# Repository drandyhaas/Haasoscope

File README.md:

# Haasoscope

Docs, design, firmware, and software for the Haasoscope!
Read the guide here: https://goo.gl/1Ry1k4 

Original funding campaign: https://www.crowdsupply.com/andy-haas/haasoscope (see the "updates" tab for lots of info)
Now also for sale on eBay - just search for "Haasoscope": https://www.ebay.com/sch/i.html?_nkw=haasoscope

A changelog for the python code is here: https://docs.google.com/document/d/18tjrI03KipmFqbNIHOzAKYy1VVE9wWbefSHazbPP8Gc/edit?usp=sharing and it also has pointers to changelogs for the firmware, board, and android app.

3D printable cases are available (see the guide for info)

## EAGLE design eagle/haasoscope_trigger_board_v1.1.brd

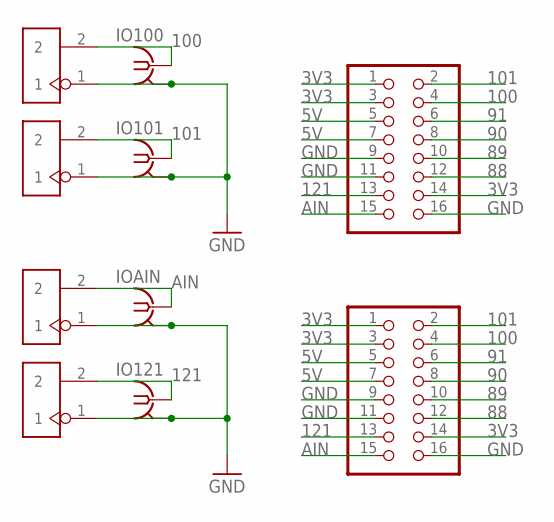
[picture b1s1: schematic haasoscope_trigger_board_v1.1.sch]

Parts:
IO100, IO101, IO121: BU-SMB-V
IOAIN: BU-SMB-V
J1, J2, J3, J4: 2p-2.54; H2-2.54
JP1: Jp1; 2X08
JP2: JP2; 2X08

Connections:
3V3: JP1.1, JP1.3, JP1.14, JP2.1, JP2.3, JP2.14
5V: JP1.5, JP1.7, JP2.5, JP2.7
88: JP1.12, JP2.12
89: JP1.10, JP2.10
90: JP1.8, JP2.8
91: JP1.6, JP2.6
100: IO100.1, J1.2, JP1.4, JP2.4
101: IO101.1, J2.2, JP1.2, JP2.2
121: IO121.1, J4.2, JP1.13, JP2.13
AIN: IOAIN.1, J3.2, JP1.15, JP2.15
GND: IO100.2, IO100.3 (2), IO100.4 (2), IO100.5 (2), IO101.2, IO101.3 (2), IO101.4 (2), IO101.5 (2), IO121.2, IO121.3 (2), IO121.4 (2), IO121.5 (2), IOAIN.2, IOAIN.3 (2), IOAIN.4 (2), IOAIN.5 (2), J1.1, J2.1, J3.1, J4.1, JP1.9, JP1.11, JP1.16, JP2.9, JP2.11, JP2.16

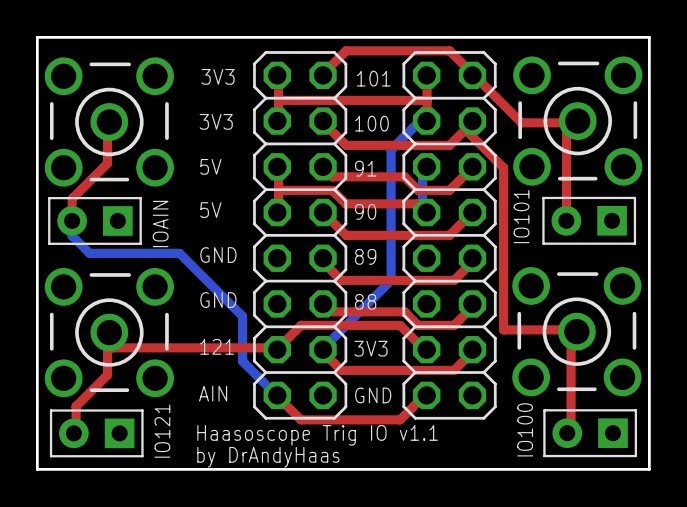
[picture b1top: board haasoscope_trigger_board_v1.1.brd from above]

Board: 2 copper layers, 34.0 x 24.0 mm, 10 parts (0 on the bottom side), 11 nets.

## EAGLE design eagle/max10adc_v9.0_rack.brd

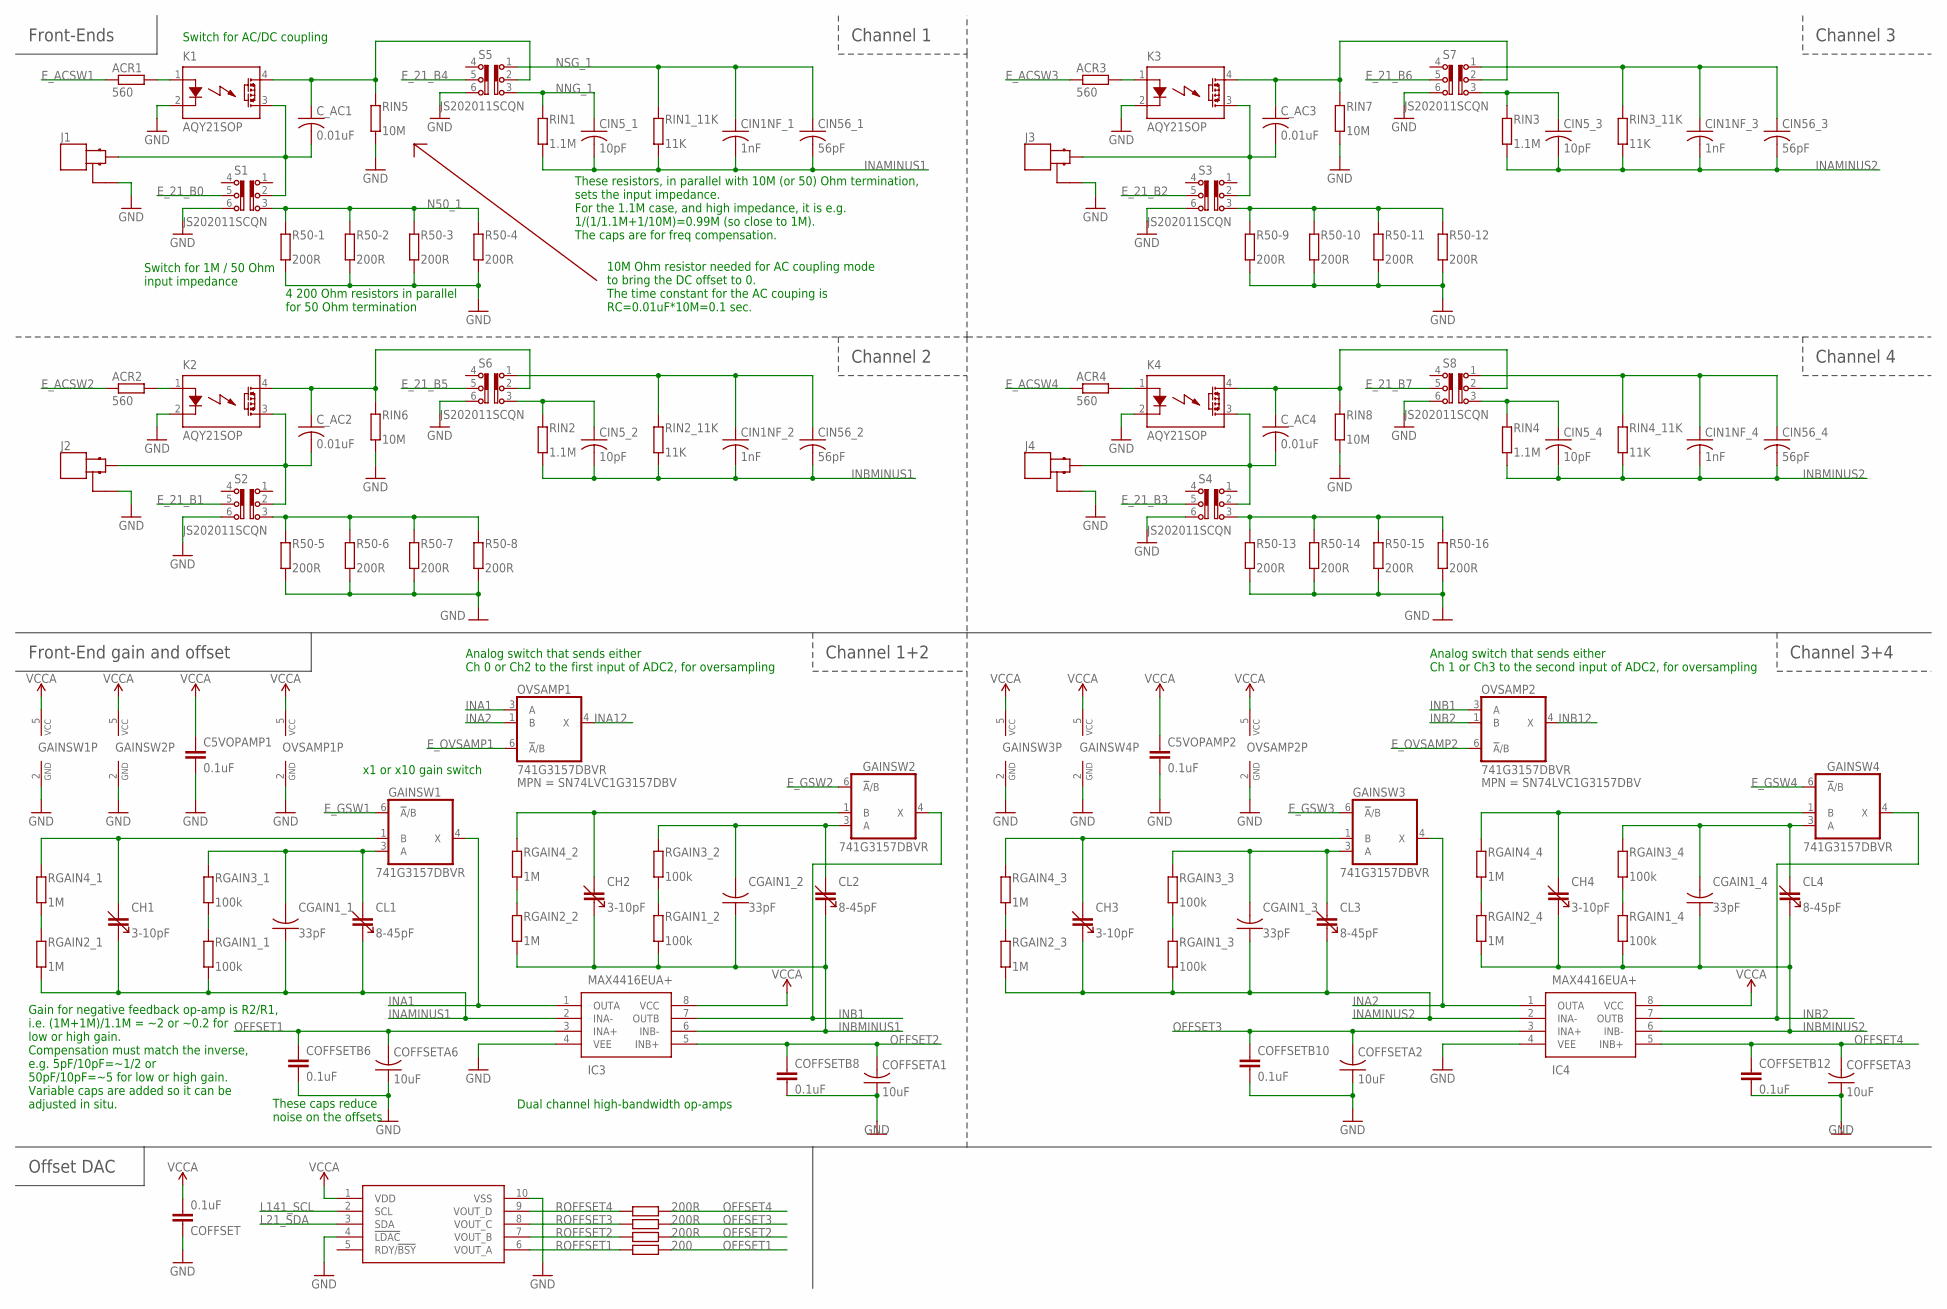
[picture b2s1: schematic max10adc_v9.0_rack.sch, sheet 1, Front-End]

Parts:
ACR1, ACR2, ACR3, ACR4: 560; R0805; MPN MF-RES-0805-560
C5VOPAMP1, C5VOPAMP2: 0.1uF; C0805K; MPN MF-CAP-0805-0.1uF
CGAIN1_1, CGAIN1_2, CGAIN1_3, CGAIN1_4: 33pF; C0603; MPN 06033A330JAT2A
CH1, CH2, CH3, CH4: 3-10pF; CTZ3; MPN TZY2Z100AC01
CIN1NF_1, CIN1NF_2, CIN1NF_3, CIN1NF_4: 1nF; C0603; MPN 06035A102JAT2A
CIN5_1, CIN5_2, CIN5_3, CIN5_4: 10pF; C0603; MPN MF-CAP-0603-10pF
CIN56_1, CIN56_2, CIN56_3, CIN56_4: 56pF; C0603; MPN 06035A560FAT2A
CL1, CL2, CL3, CL4: 8-45pF; CTZ3; MPN TZY2K450AC01
COFFSET: 0.1uF; C0805K; MPN MF-CAP-0805-0.1uF
COFFSETA1, COFFSETA2, COFFSETA3, COFFSETA6: 10uF; C1206; MPN MF-CAP-1206-10uF
COFFSETB6, COFFSETB8, COFFSETB10, COFFSETB12: 0.1uF; C0805K; MPN MF-CAP-0805-0.1uF
C_AC1, C_AC2, C_AC3, C_AC4: 0.01uF; C0603
DAC1: MCP4728; MSOP10
GAINSW1, GAINSW2, GAINSW3, GAINSW4: 741G3157DBVR; DBV_R-PDSO-G6; MPN SN74LVC1G3157DBV
IC3, IC4: MAX4416EUA+; SOP65P490X110-8N
J1, J2, J3, J4: MOLEX_BNC_73100-0105; MOLEX-BNC-73100-0105; MPN 73100-0105
K1, K2, K3, K4: AQY21SOP; SOP04; MPN AQY210S
OVSAMP1, OVSAMP2: 741G3157DBVR; DBV_R-PDSO-G6; MPN SN74LVC1G3157DBV
R50-1, R50-2, R50-3, R50-4, R50-5, R50-6, R50-7, R50-8, R50-9, R50-10, R50-11, R50-12, R50-13, R50-14, R50-15, R50-16: 200R; R0805
RGAIN1_1, RGAIN1_2, RGAIN1_3, RGAIN1_4, RGAIN3_1, RGAIN3_2, RGAIN3_3, RGAIN3_4: 100k; R0805; MPN MF-RES-0805-100k
RGAIN2_1, RGAIN2_2, RGAIN2_3, RGAIN2_4, RGAIN4_1, RGAIN4_2, RGAIN4_3, RGAIN4_4: 1M; R0805; MPN MF-RES-0805-1M
RIN1, RIN2, RIN3, RIN4: 1.1M; R0805; MPN CRCW08051M10FKEA
RIN1_11K, RIN2_11K, RIN3_11K, RIN4_11K: 11K; R0805; MPN CRCW080511K0FKEA
RIN5, RIN6, RIN7, RIN8: 10M; R0805; MPN CRCW080510M0FKEB
ROFFSET1: 200; R0805
ROFFSET2, ROFFSET3, ROFFSET4: 200R; R0805
S1, S2, S3, S4, S5, S6, S7, S8: JS202011SCQN

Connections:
CGAIN1: CGAIN1_1.2, CL1.- (4), GAINSW1.3 (A), RGAIN3_1.1
CGAIN2: CH1.- (4), GAINSW1.1 (B), RGAIN4_1.1
CGAIN3: CGAIN1_2.2, CL2.- (4), GAINSW2.3 (A), RGAIN3_2.1
CGAIN4: CH2.- (4), GAINSW2.1 (B), RGAIN4_2.1
CGAIN5: CGAIN1_3.2, CL3.- (4), GAINSW3.3 (A), RGAIN3_3.1
CGAIN6: CH3.- (4), GAINSW3.1 (B), RGAIN4_3.1
CGAIN7: CGAIN1_4.2, CL4.- (4), GAINSW4.3 (A), RGAIN3_4.1
CGAIN8: CH4.- (4), GAINSW4.1 (B), RGAIN4_4.1
E_21_B0: S1.5; also elsewhere on the board
E_21_B1: S2.5; also elsewhere on the board
E_21_B2: S3.5; also elsewhere on the board
E_21_B3: S4.5; also elsewhere on the board
E_21_B4: S5.5; also elsewhere on the board
E_21_B5: S6.5; also elsewhere on the board
E_21_B6: S7.5; also elsewhere on the board
E_21_B7: S8.5; also elsewhere on the board
E_ACSW1: ACR1.1; also elsewhere on the board
E_ACSW2: ACR2.1; also elsewhere on the board
E_ACSW3: ACR3.1; also elsewhere on the board
E_ACSW4: ACR4.1; also elsewhere on the board
E_GSW1: GAINSW1.6 (!A!/B); also elsewhere on the board
E_GSW2: GAINSW2.6 (!A!/B); also elsewhere on the board
E_GSW3: GAINSW3.6 (!A!/B); also elsewhere on the board
E_GSW4: GAINSW4.6 (!A!/B); also elsewhere on the board
E_OVSAMP1: OVSAMP1.6 (!A!/B); also elsewhere on the board
E_OVSAMP2: OVSAMP2.6 (!A!/B); also elsewhere on the board
GND: C5VOPAMP1.2, C5VOPAMP2.2, COFFSET.1, COFFSETA1.1, COFFSETA2.1, COFFSETA3.1, COFFSETA6.1, COFFSETB6.1, COFFSETB8.1, COFFSETB10.1, COFFSETB12.1, DAC1.4 (!LDAC), DAC1.10 (VSS), GAINSW1.2 (GND), GAINSW2.2 (GND), GAINSW3.2 (GND), GAINSW4.2 (GND), IC3.4 (VEE), IC4.4 (VEE), J1.GND1 (GND), J1.GND2 (GND), J2.GND1 (GND), J2.GND2 (GND), J3.GND1 (GND), J3.GND2 (GND), J4.GND1 (GND), J4.GND2 (GND), K1.2 (K), K2.2 (K), K3.2 (K), K4.2 (K), OVSAMP1.2 (GND), OVSAMP2.2 (GND), R50-1.2, R50-2.2, R50-3.2, R50-4.2, R50-5.2, R50-6.2, R50-7.2, R50-8.2, R50-9.2, R50-10.2, R50-11.2, R50-12.2, R50-13.2, R50-14.2, R50-15.2, R50-16.2, RIN5.2, RIN6.2, RIN7.2, RIN8.2, S1.6, S2.6, S3.6, S4.6, S5.6, S6.6, S7.6, S8.6; also elsewhere on the board
INA1: GAINSW1.4 (X), IC3.1 (OUTA), OVSAMP1.3 (A); also elsewhere on the board
INA2: GAINSW3.4 (X), IC4.1 (OUTA), OVSAMP1.1 (B)
INA12: OVSAMP1.4 (X); also elsewhere on the board
INAMINUS1: CGAIN1_1.1, CH1.+ (3), CIN1NF_1.2, CIN5_1.2, CIN56_1.2, CL1.+ (3), IC3.2 (INA-), RGAIN1_1.2, RGAIN2_1.2, RIN1.2, RIN1_11K.2
INAMINUS2: CGAIN1_3.1, CH3.+ (3), CIN1NF_3.2, CIN5_3.2, CIN56_3.2, CL3.+ (3), IC4.2 (INA-), RGAIN1_3.2, RGAIN2_3.2, RIN3.2, RIN3_11K.2
INB1: GAINSW2.4 (X), IC3.7 (OUTB), OVSAMP2.3 (A); also elsewhere on the board
INB2: GAINSW4.4 (X), IC4.7 (OUTB), OVSAMP2.1 (B)
INB12: OVSAMP2.4 (X); also elsewhere on the board
INBMINUS1: CGAIN1_2.1, CH2.+ (3), CIN1NF_2.2, CIN5_2.2, CIN56_2.2, CL2.+ (3), IC3.6 (INB-), RGAIN1_2.2, RGAIN2_2.2, RIN2.2, RIN2_11K.2
INBMINUS2: CGAIN1_4.1, CH4.+ (3), CIN1NF_4.2, CIN5_4.2, CIN56_4.2, CL4.+ (3), IC4.6 (INB-), RGAIN1_4.2, RGAIN2_4.2, RIN4.2, RIN4_11K.2
INJ1: C_AC1.2, J1.SIGNAL, K1.3 (DS2), S1.2
INJ2: C_AC2.2, J2.SIGNAL, K2.3 (DS2), S2.2
INJ3: C_AC3.2, J3.SIGNAL, K3.3 (DS2), S3.2
INJ4: C_AC4.2, J4.SIGNAL, K4.3 (DS2), S4.2
L21_SDA: DAC1.3 (SDA); also elsewhere on the board
L141_SCL: DAC1.2 (SCL); also elsewhere on the board
N50_1: R50-1.1, R50-2.1, R50-3.1, R50-4.1, S1.3
unnamed: RGAIN1_1.1, RGAIN3_1.2
unnamed: RGAIN2_1.1, RGAIN4_1.2
unnamed: RGAIN1_2.1, RGAIN3_2.2
unnamed: RGAIN2_2.1, RGAIN4_2.2
unnamed: RGAIN1_3.1, RGAIN3_3.2
unnamed: RGAIN2_3.1, RGAIN4_3.2
unnamed: RGAIN1_4.1, RGAIN3_4.2
unnamed: RGAIN2_4.1, RGAIN4_4.2
unnamed: C_AC1.1, K1.4 (DS1), RIN5.1, S5.2
unnamed: ACR1.2, K1.1 (A)
unnamed: C_AC2.1, K2.4 (DS1), RIN6.1, S6.2
unnamed: CIN1NF_2.1, CIN56_2.1, RIN2_11K.1, S6.1
unnamed: ACR2.2, K2.1 (A)
unnamed: CIN5_2.1, RIN2.1, S6.3
unnamed: R50-5.1, R50-6.1, R50-7.1, R50-8.1, S2.3
unnamed: R50-9.1, R50-10.1, R50-11.1, R50-12.1, S3.3
unnamed: R50-13.1, R50-14.1, R50-15.1, R50-16.1, S4.3
unnamed: ACR3.2, K3.1 (A)
unnamed: ACR4.2, K4.1 (A)
unnamed: C_AC3.1, K3.4 (DS1), RIN7.1, S7.2
unnamed: CIN1NF_3.1, CIN56_3.1, RIN3_11K.1, S7.1
unnamed: DAC1.6 (VOUT_A), ROFFSET1.2
unnamed: DAC1.7 (VOUT_B), ROFFSET2.2
unnamed: DAC1.8 (VOUT_C), ROFFSET3.2
unnamed: DAC1.9 (VOUT_D), ROFFSET4.2
unnamed: C_AC4.1, K4.4 (DS1), RIN8.1, S8.2
unnamed: CIN5_3.1, RIN3.1, S7.3
unnamed: CIN1NF_4.1, CIN56_4.1, RIN4_11K.1, S8.1
unnamed: CIN5_4.1, RIN4.1, S8.3
NNG_1: CIN5_1.1, RIN1.1, S5.3
NSG_1: CIN1NF_1.1, CIN56_1.1, RIN1_11K.1, S5.1
OFFSET1: COFFSETA6.2, COFFSETB6.2, IC3.3 (INA+), ROFFSET1.1
OFFSET2: COFFSETA1.2, COFFSETB8.2, IC3.5 (INB+), ROFFSET2.1
OFFSET3: COFFSETA2.2, COFFSETB10.2, IC4.3 (INA+), ROFFSET3.1
OFFSET4: COFFSETA3.2, COFFSETB12.2, IC4.5 (INB+), ROFFSET4.1
VCCA: C5VOPAMP1.1, C5VOPAMP2.1, COFFSET.2, DAC1.1 (VDD), GAINSW1.5 (VCC), GAINSW2.5 (VCC), GAINSW3.5 (VCC), GAINSW4.5 (VCC), IC3.8 (VCC), IC4.8 (VCC), OVSAMP1.5 (VCC), OVSAMP2.5 (VCC); also elsewhere on the board

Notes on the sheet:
Front-Ends
Channel 3
Channel 1
Channel 2
Channel 4
Front-End gain and offset
Channel 1+2
Channel 3+4
Offset DAC
4 200 Ohm resistors in parallel for 50 Ohm termination
10M Ohm resistor needed for AC coupling mode to bring the DC offset to 0. The time constant for the AC couping is RC=0.01uF*10M=0.1 sec.
These resistors, in parallel with 10M (or 50) Ohm termination, sets the input impedance. For the 1.1M case, and high impedance, it is e.g. 1/(1/1.1M+1/10M)=0.99M (so close to 1M). The caps are for freq compensation.
Switch for AC/DC coupling
Switch for 1M / 50 Ohm input impedance
Analog switch that sends either Ch 0 or Ch2 to the first input of ADC2, for oversampling
Analog switch that sends either Ch 1 or Ch3 to the second input of ADC2, for oversampling
Dual channel high-bandwidth op-amps
x1 or x10 gain switch
These caps reduce noise on the offsets
Gain for negative feedback op-amp is R2/R1, i.e. (1M+1M)/1.1M = ~2 or ~0.2 for low or high gain. Compensation must match the inverse, e.g. 5pF/10pF=~1/2 or 50pF/10pF=~5 for low or high gain. Variable caps are added so it can be adjusted in situ.

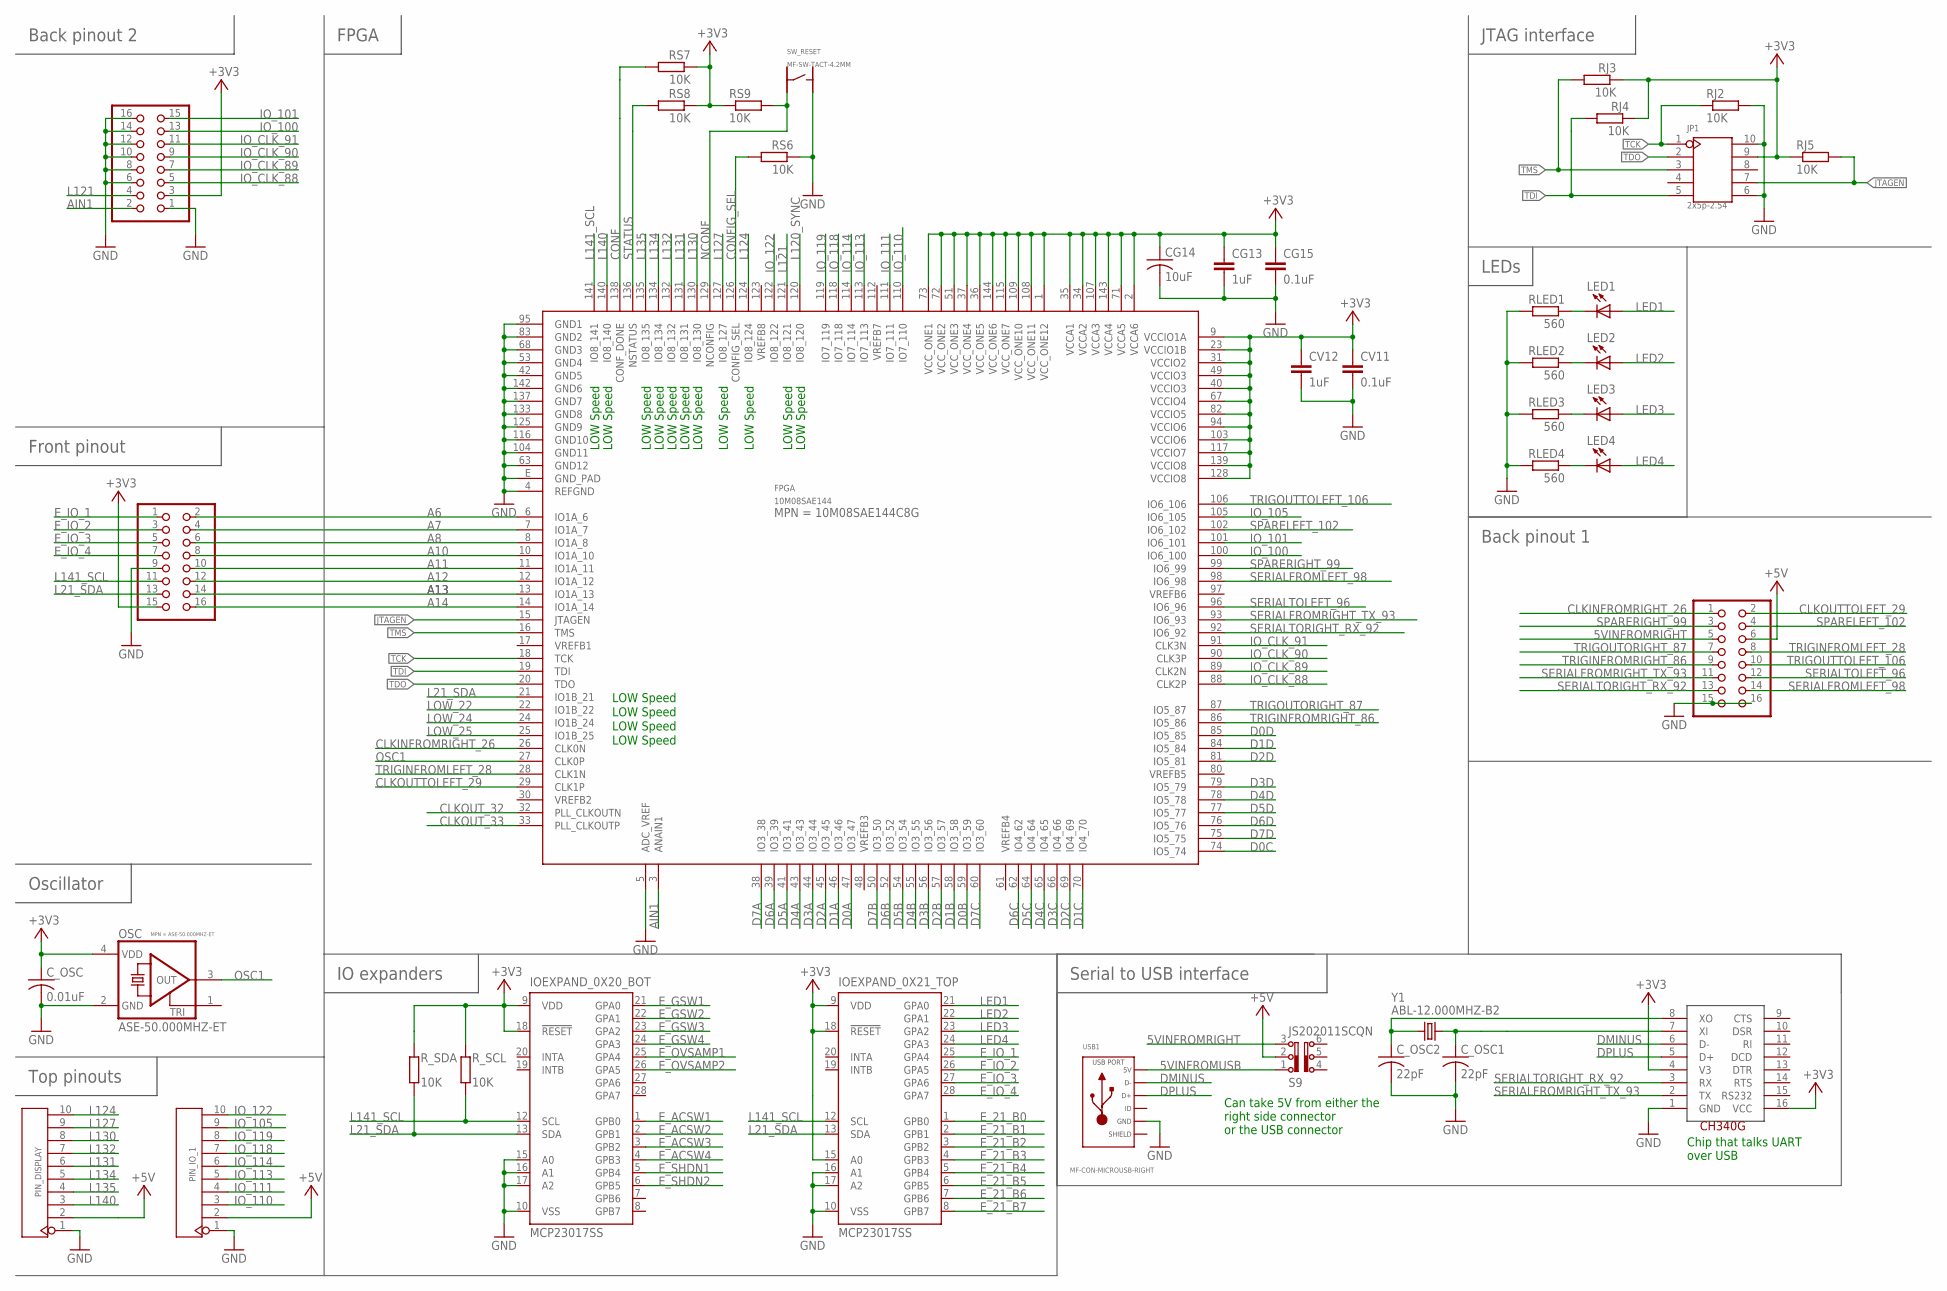
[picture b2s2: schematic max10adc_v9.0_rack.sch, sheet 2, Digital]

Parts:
CG13: 1uF; C0805K; MPN MF-CAP-0805-1uF
CG14: 10uF; C1206; MPN MF-CAP-1206-10uF
CG15: 0.1uF; C0805K; MPN MF-CAP-0805-0.1uF
CV11: 0.1uF; C0805K; MPN MF-CAP-0805-0.1uF
CV12: 1uF; C0805K; MPN MF-CAP-0805-1uF
C_OSC: 0.01uF; C0603
C_OSC1, C_OSC2: 22pF; C0603
FPGA: 10M08SAE144; EQFP144; MPN 10M08SAE144C8G
IOEXPAND_0X20_BOT, IOEXPAND_0X21_TOP: MCP23017SS; SSOP28
JP1: 2x5p-2.54; H2X5-2.54
LED1, LED2, LED3, LED4: MF-LED-0805-RED; SML0805; MPN MF-LED-0805-RED
OSC: ASE-50.000MHZ-ET; ASE; MPN ASE-50.000MHZ-ET
PIN_AIN_IO2_PWRGND: 15-91-2160; 2X08/90; MPN 15-91-2160
PIN_ANALOG_IOEXP, PIN_ANALOG_IOEXP1: 15-91-2160; 2X08/90; MPN 15-91-2160
PIN_DISPLAY: YELLOW-10P-2.54; H10-2.54
PIN_IO_1: YELLOW-10P-2.54; H10-2.54
RJ2, RJ3, RJ4, RJ5: 10K; R0805; MPN MF-RES-0805-10K
RLED1, RLED2, RLED3, RLED4: 560; R0805; MPN MF-RES-0805-560
RS6, RS7, RS8, RS9: 10K; R0805; MPN MF-RES-0805-10K
R_SCL: 10K; R0805; MPN MF-RES-0805-10K
R_SDA: 10K; R0805; MPN MF-RES-0805-10K
S9: JS202011SCQN
SW_RESET: MF-SW-TACT-4.2MM; TACT4.2MM
U340G: CH340G; SOIC16
USB1: MF-CON-MICROUSB-RIGHT; 10118193-0001LF
Y1: ABL-12.000MHZ-B2; HC49US

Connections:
5VINFROMRIGHT: PIN_ANALOG_IOEXP1.5, S9.3
5VINFROMUSB: S9.1, USB1.1 (5V)
+3V3: CG13.1, CG14.1, CG15.1, CV11.1, CV12.1, C_OSC.1, FPGA.1 (VCC_ONE12), FPGA.2 (VCCA6), FPGA.9 (VCCIO1A), FPGA.23 (VCCIO1B), FPGA.31 (VCCIO2), FPGA.34 (VCCA2), FPGA.35 (VCCA1), FPGA.36 (VCC_ONE5), FPGA.37 (VCC_ONE4), FPGA.40 (VCCIO3), FPGA.49 (VCCIO3), FPGA.51 (VCC_ONE3), FPGA.67 (VCCIO4), FPGA.71 (VCCA5), FPGA.72 (VCC_ONE2), FPGA.73 (VCC_ONE1), FPGA.82 (VCCIO5), FPGA.94 (VCCIO6), FPGA.103 (VCCIO6), FPGA.107 (VCCA3), FPGA.108 (VCC_ONE11), FPGA.109 (VCC_ONE10), FPGA.115 (VCC_ONE7), FPGA.117 (VCCIO7), FPGA.128 (VCCIO8), FPGA.139 (VCCIO8), FPGA.143 (VCCA4), FPGA.144 (VCC_ONE6), IOEXPAND_0X20_BOT.9 (VDD), IOEXPAND_0X20_BOT.18 (!RESET), IOEXPAND_0X21_TOP.9 (VDD), IOEXPAND_0X21_TOP.15 (A0), IOEXPAND_0X21_TOP.18 (!RESET), JP1.9, OSC.4 (VDD), PIN_AIN_IO2_PWRGND.3, PIN_ANALOG_IOEXP.15, RJ3.1, RJ4.1, RJ5.1, RS7.1, RS8.1, RS9.1, R_SCL.2, R_SDA.2, U340G.4 (V3), U340G.16 (VCC); also elsewhere on the board
+5V: PIN_ANALOG_IOEXP1.6, PIN_DISPLAY.2, PIN_IO_1.2, S9.2; also elsewhere on the board
A6: FPGA.6 (IO1A_6), PIN_ANALOG_IOEXP.2
A7: FPGA.7 (IO1A_7), PIN_ANALOG_IOEXP.4
A8: FPGA.8 (IO1A_8), PIN_ANALOG_IOEXP.6
A10: FPGA.10 (IO1A_10), PIN_ANALOG_IOEXP.8
A11: FPGA.11 (IO1A_11), PIN_ANALOG_IOEXP.10
A12: FPGA.12 (IO1A_12), PIN_ANALOG_IOEXP.12
A13: FPGA.13 (IO1A_13), PIN_ANALOG_IOEXP.14
A14: FPGA.14 (IO1A_14), PIN_ANALOG_IOEXP.16
AIN1: FPGA.3 (ANAIN1), PIN_AIN_IO2_PWRGND.2
CLKINFROMRIGHT_26: FPGA.26 (CLK0N), PIN_ANALOG_IOEXP1.1
CLKOUTTOLEFT_29: FPGA.29 (CLK1P), PIN_ANALOG_IOEXP1.2
CLKOUT_32: FPGA.32 (PLL_CLKOUTN); also elsewhere on the board
CLKOUT_33: FPGA.33 (PLL_CLKOUTP); also elsewhere on the board
CONF: FPGA.138 (CONF_DONE), RS7.2
CONFIG_SEL: FPGA.126 (CONFIG_SEL), RS6.2
D0A: FPGA.47 (IO3_47); also elsewhere on the board
D0B: FPGA.59 (IO3_59); also elsewhere on the board
D0C: FPGA.74 (IO5_74); also elsewhere on the board
D0D: FPGA.85 (IO5_85); also elsewhere on the board
D1A: FPGA.46 (IO3_46); also elsewhere on the board
D1B: FPGA.58 (IO3_58); also elsewhere on the board
D1C: FPGA.70 (IO4_70); also elsewhere on the board
D1D: FPGA.84 (IO5_84); also elsewhere on the board
D2A: FPGA.45 (IO3_45); also elsewhere on the board
D2B: FPGA.57 (IO3_57); also elsewhere on the board
D2C: FPGA.69 (IO4_69); also elsewhere on the board
D2D: FPGA.81 (IO5_81); also elsewhere on the board
D3A: FPGA.44 (IO3_44); also elsewhere on the board
D3B: FPGA.56 (IO3_56); also elsewhere on the board
D3C: FPGA.66 (IO4_66); also elsewhere on the board
D3D: FPGA.79 (IO5_79); also elsewhere on the board
D4A: FPGA.43 (IO3_43); also elsewhere on the board
D4B: FPGA.55 (IO3_55); also elsewhere on the board
D4C: FPGA.65 (IO4_65); also elsewhere on the board
D4D: FPGA.78 (IO5_78); also elsewhere on the board
D5A: FPGA.41 (IO3_41); also elsewhere on the board
D5B: FPGA.54 (IO3_54); also elsewhere on the board
D5C: FPGA.64 (IO4_64); also elsewhere on the board
D5D: FPGA.77 (IO5_77); also elsewhere on the board
D6A: FPGA.39 (IO3_39); also elsewhere on the board
D6B: FPGA.52 (IO3_52); also elsewhere on the board
D6C: FPGA.62 (IO4_62); also elsewhere on the board
D6D: FPGA.76 (IO5_76); also elsewhere on the board
D7A: FPGA.38 (IO3_38); also elsewhere on the board
D7B: FPGA.50 (IO3_50); also elsewhere on the board
D7C: FPGA.60 (IO3_60); also elsewhere on the board
D7D: FPGA.75 (IO5_75); also elsewhere on the board
DMINUS: U340G.6 (D-), USB1.2 (D-)
DPLUS: U340G.5 (D+), USB1.3 (D+)
E_21_B0: IOEXPAND_0X21_TOP.1 (GPB0); also elsewhere on the board
E_21_B1: IOEXPAND_0X21_TOP.2 (GPB1); also elsewhere on the board
E_21_B2: IOEXPAND_0X21_TOP.3 (GPB2); also elsewhere on the board
E_21_B3: IOEXPAND_0X21_TOP.4 (GPB3); also elsewhere on the board
E_21_B4: IOEXPAND_0X21_TOP.5 (GPB4); also elsewhere on the board
E_21_B5: IOEXPAND_0X21_TOP.6 (GPB5); also elsewhere on the board
E_21_B6: IOEXPAND_0X21_TOP.7 (GPB6); also elsewhere on the board
E_21_B7: IOEXPAND_0X21_TOP.8 (GPB7); also elsewhere on the board
E_ACSW1: IOEXPAND_0X20_BOT.1 (GPB0); also elsewhere on the board
E_ACSW2: IOEXPAND_0X20_BOT.2 (GPB1); also elsewhere on the board
E_ACSW3: IOEXPAND_0X20_BOT.3 (GPB2); also elsewhere on the board
E_ACSW4: IOEXPAND_0X20_BOT.4 (GPB3); also elsewhere on the board
E_GSW1: IOEXPAND_0X20_BOT.21 (GPA0); also elsewhere on the board
E_GSW2: IOEXPAND_0X20_BOT.22 (GPA1); also elsewhere on the board
E_GSW3: IOEXPAND_0X20_BOT.23 (GPA2); also elsewhere on the board
E_GSW4: IOEXPAND_0X20_BOT.24 (GPA3); also elsewhere on the board
E_IO_1: IOEXPAND_0X21_TOP.25 (GPA4), PIN_ANALOG_IOEXP.1
E_IO_2: IOEXPAND_0X21_TOP.26 (GPA5), PIN_ANALOG_IOEXP.3
E_IO_3: IOEXPAND_0X21_TOP.27 (GPA6), PIN_ANALOG_IOEXP.5
E_IO_4: IOEXPAND_0X21_TOP.28 (GPA7), PIN_ANALOG_IOEXP.7
E_OVSAMP1: IOEXPAND_0X20_BOT.25 (GPA4); also elsewhere on the board
E_OVSAMP2: IOEXPAND_0X20_BOT.26 (GPA5); also elsewhere on the board
E_SHDN1: IOEXPAND_0X20_BOT.5 (GPB4); also elsewhere on the board
E_SHDN2: IOEXPAND_0X20_BOT.6 (GPB5); also elsewhere on the board
GND: CG13.2, CG14.2, CG15.2, CV11.2, CV12.2, C_OSC.2, C_OSC1.2, C_OSC2.2, FPGA.4 (REFGND), FPGA.5 (ADC_VREF), FPGA.42 (GND5), FPGA.53 (GND4), FPGA.63 (GND12), FPGA.68 (GND3), FPGA.83 (GND2), FPGA.95 (GND1), FPGA.104 (GND11), FPGA.116 (GND10), FPGA.125 (GND9), FPGA.133 (GND8), FPGA.137 (GND7), FPGA.142 (GND6), FPGA.E (GND_PAD), IOEXPAND_0X20_BOT.10 (VSS), IOEXPAND_0X20_BOT.15 (A0), IOEXPAND_0X20_BOT.16 (A1), IOEXPAND_0X20_BOT.17 (A2), IOEXPAND_0X21_TOP.10 (VSS), IOEXPAND_0X21_TOP.16 (A1), IOEXPAND_0X21_TOP.17 (A2), JP1.6, JP1.10, OSC.2 (GND), PIN_AIN_IO2_PWRGND.1, PIN_AIN_IO2_PWRGND.6, PIN_AIN_IO2_PWRGND.8, PIN_AIN_IO2_PWRGND.10, PIN_AIN_IO2_PWRGND.12, PIN_AIN_IO2_PWRGND.14, PIN_AIN_IO2_PWRGND.16, PIN_ANALOG_IOEXP.9, PIN_ANALOG_IOEXP1.15, PIN_ANALOG_IOEXP1.16, PIN_DISPLAY.1, PIN_IO_1.1, RJ2.2, RLED1.2, RLED2.2, RLED3.2, RLED4.2, RS6.1, SW_RESET.P$2, U340G.1 (GND), USB1.5 (GND); also elsewhere on the board
IO_100: FPGA.100 (IO6_100), PIN_AIN_IO2_PWRGND.13
IO_101: FPGA.101 (IO6_101), PIN_AIN_IO2_PWRGND.15
IO_105: FPGA.105 (IO6_105), PIN_IO_1.9
IO_110: FPGA.110 (IO7_110), PIN_IO_1.3
IO_111: FPGA.111 (IO7_111), PIN_IO_1.4
IO_113: FPGA.113 (IO7_113), PIN_IO_1.5
IO_114: FPGA.114 (IO7_114), PIN_IO_1.6
IO_118: FPGA.118 (IO7_118), PIN_IO_1.7
IO_119: FPGA.119 (IO7_119), PIN_IO_1.8
IO_122: FPGA.122 (IO8_122), PIN_IO_1.10
IO_CLK_88: FPGA.88 (CLK2P), PIN_AIN_IO2_PWRGND.5
IO_CLK_89: FPGA.89 (CLK2N), PIN_AIN_IO2_PWRGND.7
IO_CLK_90: FPGA.90 (CLK3P), PIN_AIN_IO2_PWRGND.9
IO_CLK_91: FPGA.91 (CLK3N), PIN_AIN_IO2_PWRGND.11
JTAGEN: FPGA.15 (JTAGEN), JP1.7, RJ5.2
L21_SDA: FPGA.21 (IO1B_21), IOEXPAND_0X20_BOT.13 (SDA), IOEXPAND_0X21_TOP.13 (SDA), PIN_ANALOG_IOEXP.13, R_SDA.1; also elsewhere on the board
L120_SYNC: FPGA.120 (IO8_120); also elsewhere on the board
L121: FPGA.121 (IO8_121), PIN_AIN_IO2_PWRGND.4
L124: FPGA.124 (IO8_124), PIN_DISPLAY.10
L127: FPGA.127 (IO8_127), PIN_DISPLAY.9
L130: FPGA.130 (IO8_130), PIN_DISPLAY.8
L131: FPGA.131 (IO8_131), PIN_DISPLAY.6
L132: FPGA.132 (IO8_132), PIN_DISPLAY.7
L134: FPGA.134 (IO8_134), PIN_DISPLAY.5
L135: FPGA.135 (IO8_135), PIN_DISPLAY.4
L140: FPGA.140 (IO8_140), PIN_DISPLAY.3
L141_SCL: FPGA.141 (IO8_141), IOEXPAND_0X20_BOT.12 (SCL), IOEXPAND_0X21_TOP.12 (SCL), PIN_ANALOG_IOEXP.11, R_SCL.1; also elsewhere on the board
LED1: IOEXPAND_0X21_TOP.21 (GPA0), LED1.A
LED2: IOEXPAND_0X21_TOP.22 (GPA1), LED2.A
LED3: IOEXPAND_0X21_TOP.23 (GPA2), LED3.A
LED4: IOEXPAND_0X21_TOP.24 (GPA3), LED4.A
LOW_22: FPGA.22 (IO1B_22); also elsewhere on the board
LOW_24: FPGA.24 (IO1B_24); also elsewhere on the board
LOW_25: FPGA.25 (IO1B_25); also elsewhere on the board
unnamed: LED4.C, RLED4.1
unnamed: LED3.C, RLED3.1
unnamed: LED2.C, RLED2.1
unnamed: LED1.C, RLED1.1
unnamed: C_OSC1.1, U340G.7 (XI), Y1.1
unnamed: C_OSC2.1, U340G.8 (XO), Y1.2
NCONF: FPGA.129 (NCONFIG), RS9.2, SW_RESET.P$4
OSC1: FPGA.27 (CLK0P), OSC.3 (OUT)
SERIALFROMLEFT_98: FPGA.98 (IO6_98), PIN_ANALOG_IOEXP1.14
SERIALFROMRIGHT_TX_93: FPGA.93 (IO6_93), PIN_ANALOG_IOEXP1.11, U340G.2 (TX)
SERIALTOLEFT_96: FPGA.96 (IO6_96), PIN_ANALOG_IOEXP1.12
SERIALTORIGHT_RX_92: FPGA.92 (IO6_92), PIN_ANALOG_IOEXP1.13, U340G.3 (RX)
SLD: USB1.S1 (SLD), USB1.S2 (SLD), USB1.S3 (SLD), USB1.S4 (SLD)
SPARELEFT_102: FPGA.102 (IO6_102), PIN_ANALOG_IOEXP1.4
SPARERIGHT_99: FPGA.99 (IO6_99), PIN_ANALOG_IOEXP1.3
STATUS: FPGA.136 (NSTATUS), RS8.2
TCK: FPGA.18 (TCK), JP1.1, RJ2.1
TDI: FPGA.19 (TDI), JP1.5, RJ4.2
TDO: FPGA.20 (TDO), JP1.2
TMS: FPGA.16 (TMS), JP1.3, RJ3.2
TRIGINFROMLEFT_28: FPGA.28 (CLK1N), PIN_ANALOG_IOEXP1.8
TRIGINFROMRIGHT_86: FPGA.86 (IO5_86), PIN_ANALOG_IOEXP1.9
TRIGOUTORIGHT_87: FPGA.87 (IO5_87), PIN_ANALOG_IOEXP1.7
TRIGOUTTOLEFT_106: FPGA.106 (IO6_106), PIN_ANALOG_IOEXP1.10

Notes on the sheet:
LOW Speed
FPGA
Back pinout 2
Front pinout
Oscillator
Top pinouts
IO expanders
Serial to USB interface
LEDs
JTAG interface
Can take 5V from either the right side connector or the USB connector
Chip that talks UART over USB
Back pinout 1

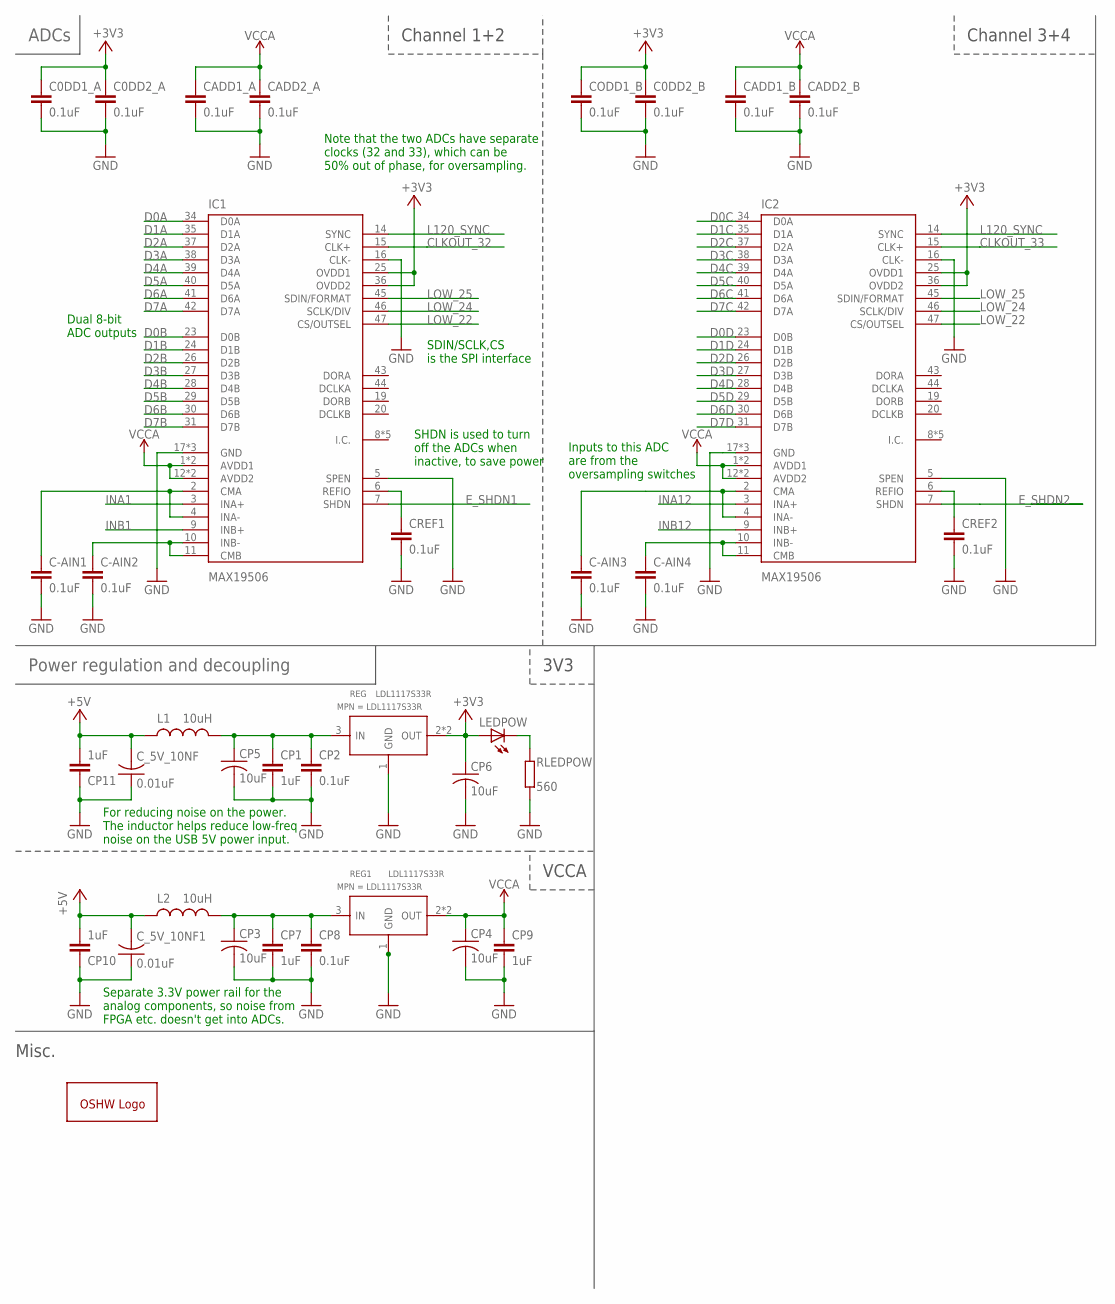
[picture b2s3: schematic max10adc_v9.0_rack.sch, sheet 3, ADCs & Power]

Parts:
C0DD1_A, C0DD2_A, C0DD2_B: 0.1uF; C0805K; MPN MF-CAP-0805-0.1uF
C-AIN1, C-AIN2, C-AIN3, C-AIN4: 0.1uF; C0805K; MPN MF-CAP-0805-0.1uF
CADD1_A, CADD1_B, CADD2_A, CADD2_B: 0.1uF; C0805K; MPN MF-CAP-0805-0.1uF
CODD1_B: 0.1uF; C0805K; MPN MF-CAP-0805-0.1uF
CP1, CP7, CP9, CP10, CP11: 1uF; C0805K; MPN MF-CAP-0805-1uF
CP2, CP8: 0.1uF; C0805K; MPN MF-CAP-0805-0.1uF
CP3, CP4, CP5, CP6: 10uF; C1206; MPN MF-CAP-1206-10uF
CREF1, CREF2: 0.1uF; C0805K; MPN MF-CAP-0805-0.1uF
C_5V_10NF, C_5V_10NF1: 0.01uF; C0603
GOLD_ORB_SM1: OSHWLOGOLOGO8MM; OSHW_8MM
IC1, IC2: MAX19506; TQFP-48; MPN MAX19506ETM+
L1, L2: 10uH; 1210; MPN MF-IND-1210-10uH
LEDPOW: MF-LED-0805-RED; SML0805; MPN MF-LED-0805-RED
REG, REG1: LDL1117S33R; SOT-223; MPN LDL1117S33R
RLEDPOW: 560; R0805; MPN MF-RES-0805-560

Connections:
+3V3: C0DD1_A.1, C0DD2_A.1, C0DD2_B.1, CODD1_B.1, CP6.1, IC1.25 (OVDD1), IC1.36 (OVDD2), IC2.25 (OVDD1), IC2.36 (OVDD2), LEDPOW.A, REG.2 (OUT), REG.TER (OUT); also elsewhere on the board
+5V: CP10.2, CP11.2, C_5V_10NF.2, C_5V_10NF1.2, L1.1, L2.1; also elsewhere on the board
CLKOUT_32: IC1.15 (CLK+); also elsewhere on the board
CLKOUT_33: IC2.15 (CLK+); also elsewhere on the board
D0A: IC1.34 (D0A); also elsewhere on the board
D0B: IC1.23 (D0B); also elsewhere on the board
D0C: IC2.34 (D0A); also elsewhere on the board
D0D: IC2.23 (D0B); also elsewhere on the board
D1A: IC1.35 (D1A); also elsewhere on the board
D1B: IC1.24 (D1B); also elsewhere on the board
D1C: IC2.35 (D1A); also elsewhere on the board
D1D: IC2.24 (D1B); also elsewhere on the board
D2A: IC1.37 (D2A); also elsewhere on the board
D2B: IC1.26 (D2B); also elsewhere on the board
D2C: IC2.37 (D2A); also elsewhere on the board
D2D: IC2.26 (D2B); also elsewhere on the board
D3A: IC1.38 (D3A); also elsewhere on the board
D3B: IC1.27 (D3B); also elsewhere on the board
D3C: IC2.38 (D3A); also elsewhere on the board
D3D: IC2.27 (D3B); also elsewhere on the board
D4A: IC1.39 (D4A); also elsewhere on the board
D4B: IC1.28 (D4B); also elsewhere on the board
D4C: IC2.39 (D4A); also elsewhere on the board
D4D: IC2.28 (D4B); also elsewhere on the board
D5A: IC1.40 (D5A); also elsewhere on the board
D5B: IC1.29 (D5B); also elsewhere on the board
D5C: IC2.40 (D5A); also elsewhere on the board
D5D: IC2.29 (D5B); also elsewhere on the board
D6A: IC1.41 (D6A); also elsewhere on the board
D6B: IC1.30 (D6B); also elsewhere on the board
D6C: IC2.41 (D6A); also elsewhere on the board
D6D: IC2.30 (D6B); also elsewhere on the board
D7A: IC1.42 (D7A); also elsewhere on the board
D7B: IC1.31 (D7B); also elsewhere on the board
D7C: IC2.42 (D7A); also elsewhere on the board
D7D: IC2.31 (D7B); also elsewhere on the board
E_SHDN1: IC1.7 (SHDN); also elsewhere on the board
E_SHDN2: IC2.7 (SHDN); also elsewhere on the board
GND: C0DD1_A.2, C0DD2_A.2, C0DD2_B.2, C-AIN1.2, C-AIN2.2, C-AIN3.2, C-AIN4.2, CADD1_A.2, CADD1_B.2, CADD2_A.2, CADD2_B.2, CODD1_B.2, CP1.2, CP2.2, CP3.2, CP4.2, CP5.2, CP6.2, CP7.2, CP8.2, CP9.2, CP10.1, CP11.1, CREF1.2, CREF2.2, C_5V_10NF.1, C_5V_10NF1.1, IC1.5 (SPEN), IC1.16 (CLK-), IC1.17 (GND), IC1.18 (GND), IC1.EP_GND (GND), IC2.5 (SPEN), IC2.16 (CLK-), IC2.17 (GND), IC2.18 (GND), IC2.EP_GND (GND), REG.1 (GND), REG1.1 (GND), RLEDPOW.2; also elsewhere on the board
INA1: IC1.3 (INA+); also elsewhere on the board
INA12: IC2.3 (INA+); also elsewhere on the board
INA-1: C-AIN1.1, IC1.2 (CMA), IC1.4 (INA-)
INA-2: C-AIN3.1, IC2.2 (CMA), IC2.4 (INA-)
INB1: IC1.9 (INB+); also elsewhere on the board
INB12: IC2.9 (INB+); also elsewhere on the board
INB-1: C-AIN2.1, IC1.10 (INB-), IC1.11 (CMB)
INB-2: C-AIN4.1, IC2.10 (INB-), IC2.11 (CMB)
L120_SYNC: IC1.14 (SYNC), IC2.14 (SYNC); also elsewhere on the board
LOW_22: IC1.47 (CS/OUTSEL), IC2.47 (CS/OUTSEL); also elsewhere on the board
LOW_24: IC1.46 (SCLK/DIV), IC2.46 (SCLK/DIV); also elsewhere on the board
LOW_25: IC1.45 (SDIN/FORMAT), IC2.45 (SDIN/FORMAT); also elsewhere on the board
unnamed: LEDPOW.C, RLEDPOW.1
unnamed: CP3.1, CP7.1, CP8.1, L2.2, REG1.3 (IN)
unnamed: CP1.1, CP2.1, CP5.1, L1.2, REG.3 (IN)
REF1: CREF1.1, IC1.6 (REFIO)
REF2: CREF2.1, IC2.6 (REFIO)
VCCA: CADD1_A.1, CADD1_B.1, CADD2_A.1, CADD2_B.1, CP4.1, CP9.1, IC1.1 (AVDD1), IC1.12 (AVDD2), IC1.13 (AVDD2), IC1.48 (AVDD1), IC2.1 (AVDD1), IC2.12 (AVDD2), IC2.13 (AVDD2), IC2.48 (AVDD1), REG1.2 (OUT), REG1.TER (OUT); also elsewhere on the board

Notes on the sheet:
ADCs
Power regulation and decoupling
3V3
VCCA
Channel 1+2
Channel 3+4
Misc.
Note that the two ADCs have separate clocks (32 and 33), which can be 50% out of phase, for oversampling.
SHDN is used to turn off the ADCs when inactive, to save power
SDIN/SCLK,CS is the SPI interface
Dual 8-bit ADC outputs
Inputs to this ADC are from the oversampling switches
For reducing noise on the power. The inductor helps reduce low-freq noise on the USB 5V power input.
Separate 3.3V power rail for the analog components, so noise from FPGA etc. doesn't get into ADCs.

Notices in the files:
parts and their libraries:
SparkFun-FreqCtrl: Licensing: Creative Commons ShareAlike 4.0 International - https://creativecommons.org/licenses/by-sa/4.0
switch-ck: Copyright (C) 2011, Bob Starr
